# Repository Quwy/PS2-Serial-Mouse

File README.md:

# PS/2 to Serial mouse adapter
Active adapter for connect PS/2 mouse to the RS232C serial port.

With this adapter you don't need to search and buy rare and expensive old serial mouse for your retro computer. Any mouse with PS/2 interface and most of simple USB-mouses will operate as Microsoft or Logitech serial mouse.

* Only 16 parts including PCB and sockets.
* Small device size.
* Simple one-layer one-side PCB.
* No SMD components.
* Common and cheap microcontroller.
* Selectable 3-button mouse protocol (Microsoft or Logitech).
* Open-source electronics and firmware.

Adapter is based on ATtiny25 microcontroller, but PCB layout and firmware source are fully compatible with whole 25/45/85 series without any changes.

There are two variants of PCB layout: with PS/2 and USB mouse socket. Both they have one-layer one-side design without VIA covering and fully ready even for manual tracing.

They are fully identical except an mouse socket type.

Note what USB version does not provide true USB host. The USB socket is only used as built-in PS/2-to-USB passive adapter.

Only universal USB+PS/2 mouse will work!

Usually it is a simple office mouse with two buttons and one clickable wheel.

Jumper is used to switch 3-button mouse protocol extensions between Microsoft and Logitech style. The 1-2 position (close to the mouse socket) mean Microsoft, 2-3 respectively Logitech. Jumper is hotplug-ready.

Since RS232C port does not provide power supply enough to feed most of PS/2 mouses, the standart "floppy-style" 4-pin MOLEX plug is used as power source (+5V line only).

Please see also [README of schematic diagramm](https://github.com/Quwy/PS2-Serial-Mouse/blob/main/Electronix/README.md) and [README of firmware section](https://github.com/Quwy/PS2-Serial-Mouse/blob/main/Firmware/README.md).

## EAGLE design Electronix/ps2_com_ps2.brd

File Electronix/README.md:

# PS2 to Serial mouse adapter electronics

Schematic diagrams and PCB layouts for both PS/2 and USB adapter variants.

## PS/2 socket

## USB socket

## Differences between RTS-only and RTS+DTR implementations.

**RTS-only** implementation listen only RTS line of the RS232C port to detect init/reset signal from the mouse driver. The DTR line is ignored. This mean not full compliance with Serial Mouse specs, but enough for most existing mouse drivers. But it does give an opportunity to preserve pin 1 of microcontroller as default RESET function and use simple and cheap ISP programmers (such as [USBASP](https://www.google.com/search?q=usbasp)) to flash IC.

In this mode resistor R4 must **NOT** be installed on PCB, and there is recommended to install resistor R1 as RESET pull-up.

**RTS+DTR** implementation as opposed to RTS-only listen both RTS and DTR signals and will compatible with any mouse driver. But this is achieved at the cost of switching pin 1 to GPIO mode and lose microcontroller's ISP function. Since fuses will flashed, only high voltage serial programming tool can be used to write the IC (including reset fuses to default state). So be very careful with fuses for RTS-DTR mode.

For RTS+DTR mode resistor R4 (0-10 Ohm or jumper wire) must be installed to PCB and R1 must **NOT** be installed.

Everything else is same in both modes.

## PCB layout features

In the both PS/2 and USB layouts socket shield is used as signal ground trace for connect mouse GND pin to adapter ground. For this reason only metal sockets must be used. Especially it concerns a PS/2 which wide available in the whole-plastic variant without an metal shield.

## PCB renders and Gerber files
https://github.com/Quwy/PS2-Serial-Mouse/tree/main/Electronix/Output

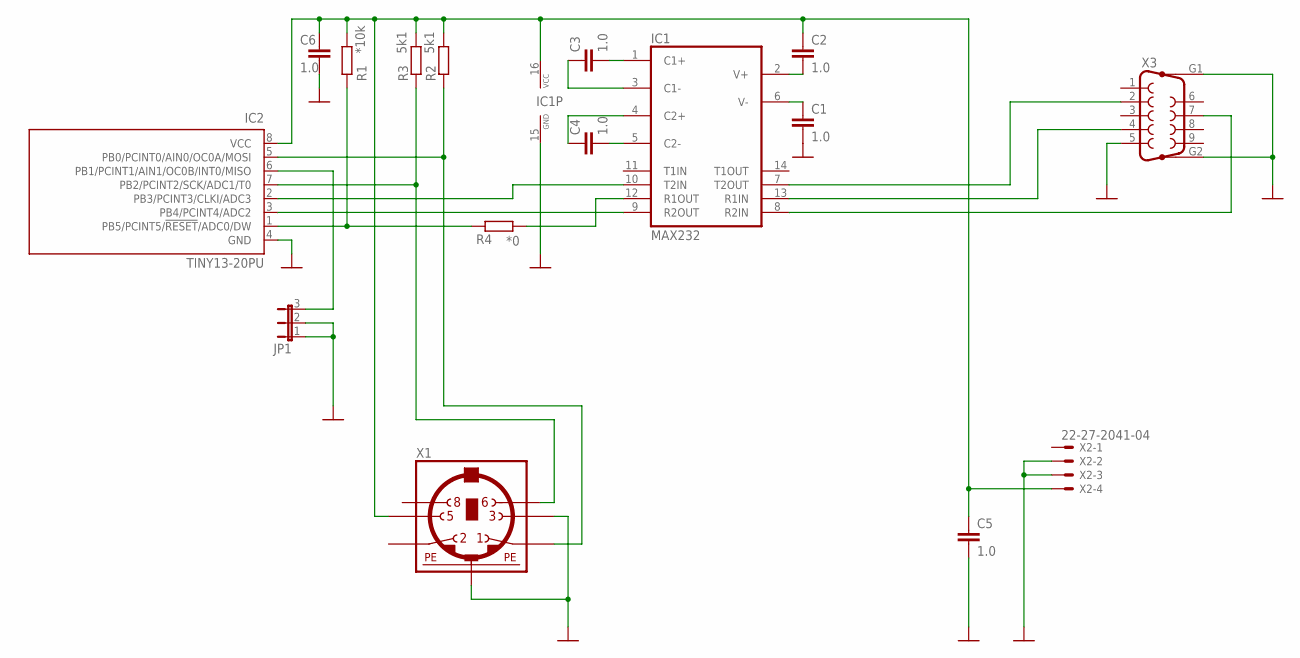
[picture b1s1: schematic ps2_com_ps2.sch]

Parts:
C1, C2, C3, C4, C5, C6: 1.0; C025-025X050
IC1: MAX232; DIL16
IC2: TINY13-20PU; DIL08
JP1: JP2E; JP2
R1: *10k; 0204/7
R2: 5k1; 0204/5
R3: 5k1; 0204V
R4: *0; 0204V
X1: MINI_DIN_6; M_DIN6
X2: 22-27-2041-04; 6410-04
X3: F09HP

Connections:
CLOCK: IC2.7 (PB2/PCINT2/SCK/ADC1/T0), R3.1, X1.6
DATA: IC2.5 (PB0/PCINT0/AIN0/OC0A/MOSI), R2.1, X1.1
DTR: IC1.13 (R1IN), X3.4
GND: C1.2, C5.2, C6.2, IC1.15 (GND), IC2.4 (GND), JP1.1, JP1.2, X1.3, X1.SH1 (PE1), X1.SH2 (PE1), X1.SH3 (PE1), X2.2, X2.3, X3.5, X3.G1, X3.G2
unnamed: C4.2, IC1.5 (C2-)
unnamed: C4.1, IC1.4 (C2+)
unnamed: C3.1, IC1.3 (C1-)
unnamed: C3.2, IC1.1 (C1+)
unnamed: C1.1, IC1.6 (V-)
unnamed: C2.2, IC1.2 (V+)
unnamed: IC2.6 (PB1/PCINT1/AIN1/OC0B/INT0/MISO), JP1.3
unnamed: IC1.12 (R1OUT), R4.1
RTS: IC1.8 (R2IN), X3.7
RXD: IC1.7 (T2OUT), X3.2
TTL_DTR: IC2.1 (PB5/PCINT5/!RESET!/ADC0/DW), R1.1, R4.2
TTL_RTS: IC1.9 (R2OUT), IC2.3 (PB4/PCINT4/ADC2)
TTL_RXD: IC1.10 (T2IN), IC2.2 (PB3/PCINT3/CLKI/ADC3)
VCC: C2.1, C5.1, C6.1, IC1.16 (VCC), IC2.8 (VCC), R1.2, R2.2, R3.2, X1.5, X2.4

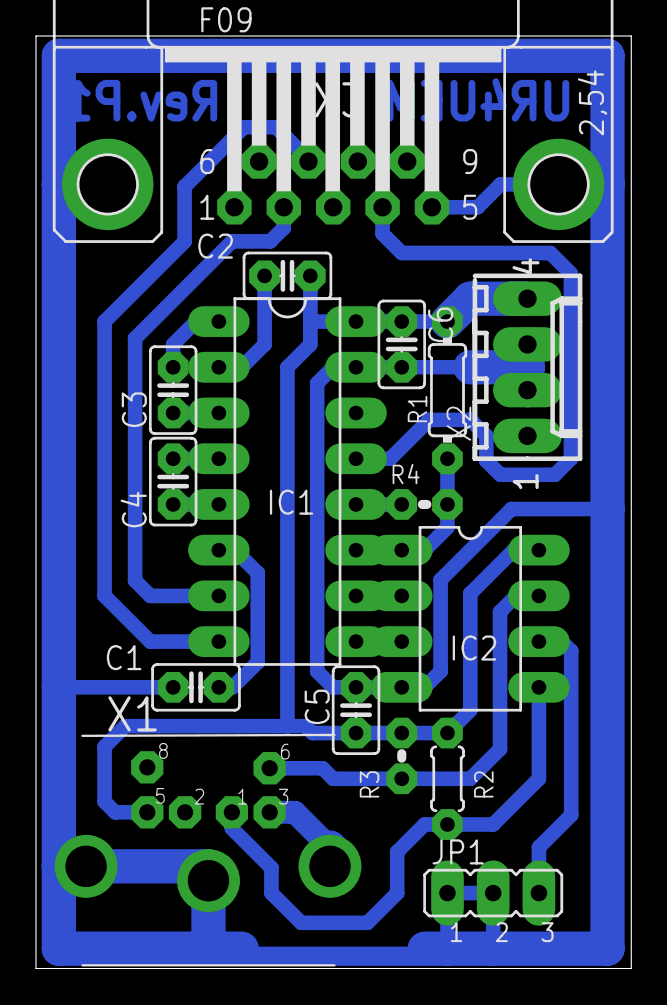
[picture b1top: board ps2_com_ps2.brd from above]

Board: 2 copper layers, 33.1 x 51.8 mm, 16 parts (0 on the bottom side), 18 nets.

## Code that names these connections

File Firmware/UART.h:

/*
 * UART.h
 *
 * UART simplified (TX-only) driver
 * 
 * Author: Mike Cherkes, UR4UEM
 *
 */ 

#ifndef UART_H_
#define UART_H_

#include <avr/interrupt.h>
#include <avr/io.h>
#include <stdint.h>
#include <stdbool.h>

#include "Defines.h"
#include "BufProc.h"

#define UART_TX_BUFFER_SIZE (4 * 3) // 3 packets of 3-button mouse or 4 packets of 2-button mouse

#ifdef UART_HI_BPS
  #ifndef UART_19200_BPS
    #define UART_BPS_CORRECTION (-1) // measured on the real hardware
  #else
    #define UART_BPS_CORRECTION (-2) // measured on the real hardware
  #endif
#else
  #define UART_BPS_CORRECTION (+8) // measured on the real hardware
#endif

typedef enum {
    UART_STAGE_IDLE,
    UART_STAGE_TX_START_BIT,
    UART_STAGE_TX_DATA,
    UART_STAGE_TX_STOP_BIT,
    UART_STAGE_TX_FINISH // second stop bit (as recommended)
} uart_stage_t;

static volatile uint8_t uart_current_byte; // current transmitted byte
static volatile uint8_t uart_current_bit; // current transmitted bit
static volatile uint8_t uart_tx_buffer[UART_TX_BUFFER_SIZE]; // TX buffer
static volatile uint8_t uart_tx_buffer_size = 0; // actual size of TX data
static volatile uart_stage_t uart_stage = UART_STAGE_IDLE; // protocol stage

static inline void uart_init(void) {
    // Pins init
    PORTB &= ~(1 << PB4); // disable pull-up for pin 3 (PB4/RTS)
    DDRB &= ~(1 << DDB4); // set pin 3 (PB4/RTS) as input
    #ifdef RESET_AS_DTR
    PORTB &= ~(1 << PB5); // disable pull-up for pin 1 (PB5/DTR)
    DDRB &= ~(1 << DDB5); // set pin 1 (PB5/DTR) as input
    #endif
    PORTB |= (1 << PB3); // set pin 2 (PB3/RXD) to "high" idle state
    DDRB |= (1 << DDB3); // set pin 2 (PB3/RXD) as output

    // Timer0 init
    TCCR0A |= (1 << WGM01); // set Timer0 CTC mode: top value is OCR0A
    TIMSK |= (1 << OCIE0A); // enable compare match interrupt with OCR0A (TIMER0_COMPA_vect)

    // Interrupts init
    PCMSK |= (1 << PCINT4); // enable pin 3 (PB4/RTS) change interrupt
    #ifdef RESET_AS_DTR
    PCMSK |= (1 << PCINT5); // enable pin 1 (PB5/RESET/DTR) change interrupt
    #endif
}

// start UART timer
static void uart_start_timer(void) {
    TCNT0 = 0; // reset timer counter
    #ifdef UART_HI_BPS
    #ifndef UART_19200_BPS
    OCR0A = 208 + UART_BPS_CORRECTION; // set top value for 9600 bps (2 000 000 / 9 600) = 208 (plus correction from the real device sample)
    #else
    OCR0A = 104 + UART_BPS_CORRECTION; // set top value for 19200 bps (2 000 000 / 19200) = 104 (plus correction from the real device sample)
    #endif
    TCCR0B |= (1 << CS01); // start timer with prescaler /8 (16 000 000 / 8 = 2 000 000 increments/sec)
    #else
    OCR0A = 208 + UART_BPS_CORRECTION; // set top value for 1200 bps (250 000 / 1200) = 208 (plus correction from the real device sample)
    TCCR0B |= (1 << CS00) | (1 << CS01); // start timer with prescaler /64 (16 000 000 / 64 = 250 000 increments/sec)
    #endif
}

// stop UART timer
static void uart_stop_timer(void) {
    TCCR0B &= ~(1 << CS00) & ~(1 << CS01) & ~(1 << CS02); // stop timer clock
}

// check for PC ready to communicate with mouse
static inline bool uart_host_active(const uint8_t PORT) {
    #ifdef RESET_AS_DTR
    return ((PORT & ((1 << PB4) | (1 << PB5))) == 0); // check for "low" on pins 3 (PB4/RTS), 1 (PB5/RESET/DTR), equialent of ((PORT & (1 << PB4)) == 0) && ((PORT & (1 << PB5)) == 0)
    #else
    return ((PORT & (1 << PB4)) == 0); // check for "low" on pin 3 (PB4/RTS)
    #endif
}

// start transmitting
static void uart_start_byte_tx() {
    if(uart_stage == UART_STAGE_IDLE && uart_host_active(PINB)) { // start TX only if idle and PC terminal is active
        uart_stage = UART_STAGE_TX_START_BIT; // first stage to form TX start condition
        uart_current_byte = buf_get_byte(uart_tx_buffer, &uart_tx_buffer_size); // extract next byte from TX buffer
        uart_current_bit = 0; // low bit first
        uart_start_timer(); // start transmitting
    }
}

// interface function to transmit a byte
static void uart_tx(const uint8_t byte) {
    buf_set_byte(byte, uart_tx_buffer, &uart_tx_buffer_size, UART_TX_BUFFER_SIZE); // extract next byte from buffer
    uart_start_byte_tx(); // start transmitting
}

// set state of TX data line
static void uart_set_tx(const bool state) {
    if(state) {
        PORTB |= (1 << PB3); // pin 2 (PB3/TX) to "high"
    } else {
        PORTB &= ~(1 << PB3); // pin 2 (PB3/TX) to "low"
    }
}

// check for bytes in the buffer and start TX if any
static void uart_process_tx(void) {
    if(uart_tx_buffer_size > 0) { // if buffer not empty
        uart_start_byte_tx();
    }
}

// abort any transmitting and clear buffers (usually if terminal becomes inactive)
static void uart_abort(void) {
    uart_stage = UART_STAGE_IDLE; // transmission aborted
    uart_stop_timer(); // stop UART clock timer
    uart_set_tx(true); // set TX line idle state
    uart_tx_buffer_size = 0; // clear TX buffer
}

// check for available space in the TX buffer
static inline uint8_t uart_tx_room(void) {
    return UART_TX_BUFFER_SIZE - uart_tx_buffer_size;
}

// UART clock timer handler
ISR(TIMER0_COMPA_vect) {
    switch(uart_stage) {
        case UART_STAGE_TX_START_BIT: // generate start bit delay
            uart_stage = UART_STAGE_TX_DATA; // next stage after delay finished
            uart_set_tx(false); // start bit always "low"
            break;

        case UART_STAGE_TX_DATA: // data stage
            uart_set_tx((uart_current_byte & (1 << uart_current_bit)) != 0); // set TX line according to current bit
            if(++uart_current_bit == 7) { // if last (7-th) bit was populated on TX line
                uart_stage = UART_STAGE_TX_STOP_BIT; // set next stage
            }
            break;

        case UART_STAGE_TX_STOP_BIT: // generate first stop bit delay
            uart_stage = UART_STAGE_TX_FINISH; // set next stage
            uart_set_tx(true); // stop bit always "high"
            break;

        case UART_STAGE_TX_FINISH: // second stop bit finished
        default: // if any unexpected state passed
            uart_stage = UART_STAGE_IDLE; // transmission finished
            uart_set_tx(true); // set TX line idle state
            uart_stop_timer(); // stop UART clock timer
            uart_process_tx(); // check buffer for next byte and start transmitting if any
    }
}

#endif /* UART_H_ */

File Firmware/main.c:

/*
 * main.c
 *
 * Main module
 * 
 * Author: Mike Cherkes, UR4UEM
 *
 */ 

#include "Defines.h"

#include <avr/io.h>
#include <avr/interrupt.h>
#include <avr/sleep.h>
#include <avr/wdt.h>
#include <stdint.h>
#include <stdbool.h>

#if defined(START_MARKER)
#include <util/delay.h>
#endif

#include "PS2_mouse.h"
#include "UART_mouse.h"

#define INITIAL_PINB ((1 << PB0) | (1 << PB2) | (1 << PB4)) // initial state of pins on PORTB (initial value assumes high levels on the SDA ans SCL as bus idle state, high on RTS as no terminal connected)

typedef enum {
    TERMINAL_STATE_INACTIVE,
    TERMINAL_STATE_PENDING,
    TERMINAL_STATE_ACTIVE
} terminal_state_t;

static volatile terminal_state_t terminal_state;
static volatile bool terminal_tx_ext_id = false;

// init watchdog
static inline void wdt_init(void) {
    WDTCR = (1 << WDCE) | (1 << WDE); // watchdog preparing
    WDTCR = (1 << WDIE) | WDTO_60MS; // setup watchdog to interrupt mode every 60 ms
}

// init GPIO system
static inline void gpio_init(void) {
    
    #ifdef START_MARKER // start marker for logic analizer trigger
    DDRB |= (1 << DDB3);
    _delay_us(10);
    DDRB &= ~(1 << DDB3);
    #endif

    GIMSK |= (1 << PCIE); // Enable pin changes interrupt
}

// init MCU
static inline void mcu_init(void) {
    sleep_enable(); // prepare sleep mode
    set_sleep_mode(SLEEP_MODE_IDLE); // SLEEP_MODE_IDLE allows to handle all necessary events
    sei(); // enable interrupts

    #ifdef PROTEUS // Proteus incorrectly simulates PLL clock (set 64 MHz instead of 16 MHz)
    CLKPR |= (1 << CLKPCE); // enable system clock prescaler
    CLKPR = (1 << CLKPS1);  // set prescaler for /4
    #endif
}

// pin change event local handler
static inline void main_PCINT0(const uint8_t prev_PINB) {
    if(uart_host_active(prev_PINB) && !uart_host_active(PINB)) { // if terminal ready pins changed state from "ready" to "not ready"
        switch(terminal_state) {
            case TERMINAL_STATE_ACTIVE: // if terminal was active, stopping all and deactivate terminal state
                uart_mouse_stop();
                ps2_mouse_stop(); // reset mouse and stop PS2 communication
                terminal_tx_ext_id = false;
                terminal_state = TERMINAL_STATE_INACTIVE;
                break;

            case TERMINAL_STATE_PENDING: // if terminal in pending state, just reset state to inactive
                terminal_state = TERMINAL_STATE_INACTIVE;
                break;

            default: // nothing to do if terminal already inactive
                break;
        }
    }
}

// perform periodic checks and tasks
static inline void main_timer_process(void) {
    switch(terminal_state) {
        case TERMINAL_STATE_PENDING: // if terminal state remains pending whole WDT timer delay, set terminal ready state
            terminal_state = TERMINAL_STATE_ACTIVE;
            ps2_mouse_start(); // init PS/2 mouse and start communication
            break;

        case TERMINAL_STATE_INACTIVE: // if terminal state is inactive
            if(uart_host_active(PINB)) { // check pins
                terminal_state = TERMINAL_STATE_PENDING; // set sdtate to pending if pins in the active state
            }
            break;

        default: // if terminal is active or unknown state, do nothing
            break;
    }

    if(terminal_tx_ext_id && terminal_state == TERMINAL_STATE_ACTIVE) {
        uart_mouse_tx_ext_id(); // send extended id if terminal is active and primary id already sent
        terminal_tx_ext_id = false;
    }
}


// main function
int main(void) {
    const ps2_mouse_state_t *ps2_mouse_state;
    
    gpio_init();
    mcu_init();
    uart_mouse_init();
    ps2_mouse_init(&ps2_mouse_state); // init PS2 mouse and get mouse data pointer
    wdt_init();
    
    #ifndef DUMMY_TEST_MODE

    terminal_state = (uart_host_active(PINB) ? TERMINAL_STATE_PENDING : TERMINAL_STATE_INACTIVE); // initial terminal state

    // main event loop
    while(true) {
        sleep_cpu(); // always try to avoid free-running main loop, use sleep mode if no current tasks

        ps2_mouse_process(terminal_state != TERMINAL_STATE_ACTIVE); // process mouse events if PC terminal is active
        
        if(ps2_mouse_responce_ok()) { // if init mouse response is "OK"
            uart_mouse_tx_id(); // send primary mouse id to port
            terminal_tx_ext_id = true; // reload external id send flag
        }

        if(ps2_mouse_was_updated()) { // if mouse data updated
            uart_mouse_tx_event(ps2_mouse_state->DX, ps2_mouse_state->DY, ps2_mouse_state->left, ps2_mouse_state->right, ps2_mouse_state->middle); // sent UART packet with ioncoming data
        }
    }

    #else

    #ifndef UART_HI_BPS
    ps2_tx(0xF3); // set report rate
    ps2_tx(20); // in 1200 bps mode only 20 reports per second fit into UART bandwidth
    #endif

    ps2_tx(0xF4); // start auto reporting

    // main event loop
    while(true) {
        sleep_cpu();

        // repeat all PS/2 outgoing data to the UART
        while(ps2_rx_count() > 0) {
            uart_tx(ps2_rx());
        }
    }

    #endif
}

// pin change interrupt handler (general for all modules)
ISR(PCINT0_vect) {
    static uint8_t prev_PINB = INITIAL_PINB;

    GIFR |= (1 << PCIF); // clear interrupt flag

    ps2_PCINT0(prev_PINB); // call PS/2 pin change handler
    main_PCINT0(prev_PINB); // call main pin change handler

    prev_PINB = PINB; // save prior port state
}

// watchdog interrupt handler
ISR(WDT_vect) {
    WDTCR |= (1 << WDIE); // important to renew WDIE bit in each call (reset will performed if no WDIE bit at next watchdog "tick")

    #ifndef DUMMY_TEST_MODE
    main_timer_process(); // UART scheduled events dispatcher
    #endif
}

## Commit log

2025-07-18 Add files via upload
    v1.10: Added 19200 bps UART rate
2025-07-18 Update Defines.h
    Disable RESET_AS_DTR by default
